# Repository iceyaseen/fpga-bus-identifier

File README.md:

# FPGA Communication Checker

A tool for figuring out how an unknown chip talks before you know anything about it. The usual situation: you have a small component with 3 or 4 pins, no datasheet, and no idea which protocol it speaks or what each pin does. Instead of guessing, you hook it up to this board and look at what actually happens on the lines.

## Status

The FPGA side is still in progress.

Working today:
- Edge capture on two probe channels, timestamped and streamed to a Python host over UART at 921600 baud.
- A framed, checksummed, self-resynchronising UART protocol between the FPGA and the host (start/stop/reset/status commands, edge records, ACK/ERROR replies).
- A from-scratch UART tx/rx pair, built and tested on the Tang Nano 9K.
- A 256-entry, block-RAM-backed capture FIFO, with high-water mark reported in the status reply.
- A PySide6 + pyqtgraph host GUI (dark instrument theme): live or offline (loaded from CSV) waveform view with pan/zoom/cursor/two draggable markers, a log-scale/zoomable pulse-width histogram, CSV export, and a "protocol hint" panel that reads the dominant pulse width and reports the closest matching clock/UART baud/1-Wire pulse - timing arithmetic only, not protocol decoding.
- An active I2C master: bidirectional open-drain probe drivers, software-switchable pull-ups, an electrical pre-scan (own pull-up / needs ours / held low / floating, per channel, before any bus traffic), and a 0x08-0x77 address sweep that reports every address that ACKs. Driven from the host's "Scan I2C" button; verified in simulation against a fake I2C slave (exactly one address found, START/STOP/ACK timing checked against spec) and confirmed on real hardware against an MLX90614 at 0x5A.

Not built yet:
- Reading actual data back from a found device (the I2C master currently only does the one-byte address-probe transaction a scan needs).
- Decoders for UART, 1-Wire, and PWM.
- Detection of analog (non-digital) devices - everything so far assumes the thing on the probes is digital.

## Host software

Requires Python 3 plus:
```
pip install PySide6 pyqtgraph pyserial
```
Then run:
```
python3 host/host.py [serial-port]
```
`host/protocol.py` holds the wire-format parser (framing, checksums, resync) and `host/hint.py` the protocol-hint arithmetic; both are plain Python with no GUI dependency, and each has a standalone test script (`host/test_frame_parser.py`, `host/test_hint.py`) that can be run without any hardware attached.

<p align="center">

<br>
<sup>Screenshot of a real capture, probed on P_A/P_B. Numbered callouts below.</sup>
</p>

1. **Sidebar** - connect, start/stop/reset capture, load/save CSV, show/hide the console.
2. **Waveform navigation** - zoom in/out, a window-width field with an adaptive ns/us/ms/s unit, step left/right, and Follow Latest (an oscilloscope-style roll-mode toggle, lit up green when on).
3. **Waveform view** - P_A/P_B drawn as square waves. Pan/zoom with the mouse, a crosshair cursor that follows it, and two draggable markers (dashed lines) with a live delta-t readout below the plot.
4. **Pulse-width histogram** - log-scale count axis, so a rare sharp spike (e.g. a 100 kHz clock) stays visible next to a much taller structureless smear instead of being flattened to nothing; the time axis is independently zoomable to reveal fine structure.
5. **Statistics + Protocol Hint** - live edge/pulse/gap stats, plus a hint that reads the histogram's dominant pulse width and checks it against known clocks, standard UART bauds, and 1-Wire timing. Pure arithmetic, never a claim to have identified a protocol - see the disclaimer printed under it.
6. **Console** (hidden by default) - the scrolling log, a raw-byte diagnostic mode, pause (freezes the view without losing anything), and clear.
7. **Status strip** - a link-alive dot that blinks while connected, live records/sec, FIFO high-water mark, a sticky overflow-since-reset dot, and the frame resync count (flagged only if resyncs happen well after connecting, not for the one-time settle that's normal when the FPGA is already transmitting at connect time).

## The PCB

A shield that sits on top of the Tang Nano 9K. Built and working, not just designed - the photos below are the real board. It has two probe channels and a 4-pin socket for the device under test.
<p align="center">

<br>
Each part on the probe lines is there for a specific reason:
</p>

- **220 ohm series resistor** on each probe line. The tool is meant to connect to devices whose voltage and drive strength are unknown, so the series resistor limits current if something unexpected is being driven.
- **Schottky clamp diodes (1N5819)** to 3.3V and GND on each probe line, so an over-voltage device can't reach the FPGA pin directly. Schottky specifically, not an ordinary diode: an ordinary diode clamps around 4.0V, which is already too high for this FPGA's inputs.
- **4.7k pull-ups switched by P-channel MOSFETs.** This is the part that needs explaining: to find out whether an unknown device already has its own pull-up, you need to disconnect ours first and see what the line does on its own. A fixed pull-up would make that measurement impossible, so it's switchable instead.
- **10k gate-to-source resistors** on those MOSFETs, so they stay off during the few milliseconds after power-up while the FPGA is still loading its bitstream and its pins are floating.

## Pin assignments

| Tang Nano 9K pin | Signal    | Notes |
|---|---|---|
| 54 | `ctrl_b`   | Active low. Pulling low turns on channel B's pull-up MOSFET. |
| 55 | `ctrl_a`   | Active low. Pulling low turns on channel A's pull-up MOSFET. |
| 56 | `probe_a`  | Probe channel A. |
| 57 | `probe_b`  | Probe channel B. |

Active low because these drive P-channel MOSFETs, which turn on when their gate is pulled low.

## Using it

Plug the unknown device into the 4-pin socket. A 4-pin device fills all four positions. A 3-pin device leaves `probe_a` empty.

## I2C scanning

Click **Scan I2C** in the host app. It runs two steps automatically:

1. **Electrical pre-scan** - before any bus traffic, each channel is classified purely by watching pull-up behaviour: *has its own pull-up* (reads high with ours off), *needs ours* (low/floating with ours off, clean high once ours switches on), *held low* (still low even with our pull-up on - a device driving it, or a short), or *floating* (unstable with no pull-up at all - nothing connected). This tells you whether the device is even I2C-shaped before wasting time on an address sweep.
2. **Address sweep** - START, address + write bit, check for ACK, STOP, for every address 0x08-0x77 (the valid 7-bit range). Every address that ACKs gets reported; an empty result is reported as "No devices found", not left ambiguous.

**Which probe is SDA and which is SCL is not auto-detected** - it's a host-side toggle ("SDA/SCL mapping: Normal (A=SDA, B=SCL) / Swapped (A=SCL, B=SDA)"), simpler and more transparent than guessing. If a scan against a known-good device finds nothing, flip the mapping and scan again. Verified against a real MLX90614 infrared thermometer (address 0x5A) on real hardware.

The scan's own generated I2C traffic is visible in the waveform view too (make sure capture is running - the "Scan I2C" button starts it automatically) - a good way to confirm the master is generating correct signals, not just trusting the reported result.

New host commands, single bytes like the existing ones (no framing needed on that side):

| Command | Effect |
|---|---|
| `A` / `a` | channel A pull-up on / off |
| `B` / `b` | channel B pull-up on / off |
| `N` / `W` | normal / swapped SDA-SCL pin mapping |
| `E` | run the electrical pre-scan |
| `I` | run the address sweep |

`E` and `I` are long-running, so unlike every other command their ACK is deferred until the operation actually finishes, not when the byte arrives - that's what lets the host safely chain pre-scan -> sweep off the pre-scan's own ACK. Two new frame types carry the results: `0xA9 PRESCAN_RESULT` (channel, category) and `0xAA ADDR_HIT` (one address that ACKed) - see `host/protocol.py` for the exact wire format, which follows the same `[MARKER][PAYLOAD][CHECKSUM]` scheme as everything else.

## Screenshots

<p align="center">

<br>
<sup>A real scan: the pre-scan found a pull-up already present on both channels, and the address sweep found one device, at 0x5A - a real MLX90614 infrared thermometer.</sup>
</p>

<p align="center">

<br>
<sup>The Tang Nano 9K wired up on a breadboard while testing against a real MLX90614.</sup>
</p>

General decoupling notes for this kind of breadboard setup: keep the 10uF bulk capacitor close to the 3.3V and GND rails it's decoupling, and keep the 100nF ceramic capacitor close to the sensor under test, not back at the FPGA end - it's there to filter noise right at the device, and a long lead defeats the point.

| Signal | Tang Nano 9K pin | Goes to |
|---|---|---|
| `probe_a` | 56 | Sensor SDA or SCL (depends on the SDA/SCL mapping setting) |
| `probe_b` | 57 | Sensor SCL or SDA (the other line) |
| `ctrl_a` | 55 | Channel A pull-up MOSFET gate |
| `ctrl_b` | 54 | Channel B pull-up MOSFET gate |
| 3.3V | - | Sensor VDD |
| GND | - | Sensor GND, common return |

Waveform and pulse-width-histogram screenshots of real captured I2C traffic, plus a contact-bounce histogram for comparison, are still to come - they need the hardware connected and, for the bounce case, a saved capture that doesn't exist yet.

## Known limitations

- Only single-ended protocols are in scope. CAN and RS-485 are differential and need a transceiver, so they're not supported.
- A completely unpowered unknown chip can't be identified from the outside. This tool only works on devices that respond when probed.
- There are two probe channels, so SPI (which needs more lines) isn't reachable yet.
- The protocol hint only measures timing. A 100 kHz clock could be I2C or SPI - the hint says "consistent with", it does not identify the protocol.

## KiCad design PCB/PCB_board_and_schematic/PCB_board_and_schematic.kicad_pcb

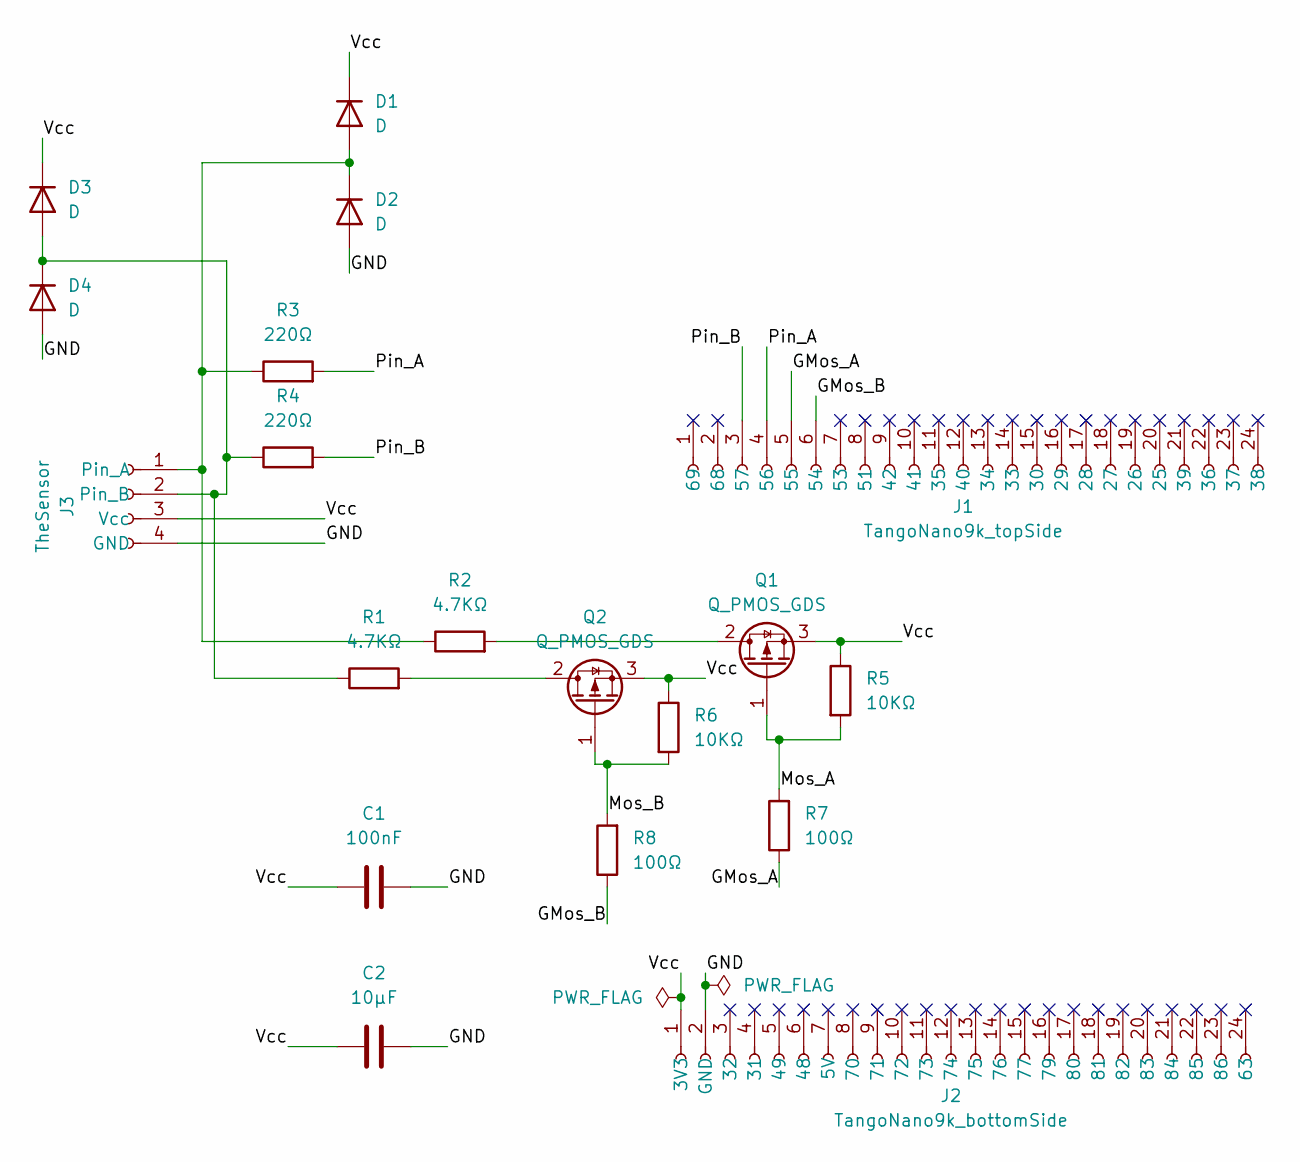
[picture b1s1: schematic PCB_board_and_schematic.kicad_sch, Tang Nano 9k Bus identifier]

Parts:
C1: 100nF; CP_Radial_D4.0mm_P1.50mm
C2: 10µF; CP_Radial_D5.0mm_P2.50mm
D1, D2, D3, D4: D; D_A-405_P7.62mm_Horizontal
J1: TangoNano9k_topSide; PinSocket_1x24_P2.54mm_Vertical
J2: TangoNano9k_bottomSide; PinSocket_1x24_P2.54mm_Vertical
J3: TheSensor; PinSocket_1x04_P2.54mm_Vertical
Q1, Q2: Q_PMOS_GDS; TO-220-3_Vertical
R1, R2: 4.7KΩ; R_Axial_DIN0204_L3.6mm_D1.6mm_P7.62mm_Horizontal
R3, R4: 220Ω; R_Axial_DIN0204_L3.6mm_D1.6mm_P7.62mm_Horizontal
R5, R6: 10KΩ; R_Axial_DIN0204_L3.6mm_D1.6mm_P7.62mm_Horizontal
R7, R8: 100Ω; R_Axial_DIN0204_L3.6mm_D1.6mm_P7.62mm_Horizontal

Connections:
/GMos_A: J1.5 (55), R7.1
/GMos_B: J1.6 (54), R8.1
/GND: C1.2, C2.2, D2.2 (A), D4.2 (A), J2.2 (GND), J3.4 (GND)
/Mos_A: Q1.1 (G), R5.2, R7.2
/Mos_B: Q2.1 (G), R6.2, R8.2
/Pin_A: J1.4 (56), R3.2
/Pin_B: J1.3 (57), R4.2
/Vcc: C1.1, C2.1, D1.1 (K), D3.1 (K), J2.1 (3V3), J3.3 (Vcc), Q1.3 (S), Q2.3 (S), R5.1, R6.1
unnamed: D1.2 (A), D2.1 (K), J3.1 (Pin_A), R2.1, R3.1
unnamed: D3.2 (A), D4.1 (K), J3.2 (Pin_B), R1.1, R4.1
unnamed: Q1.2 (D), R2.2
unnamed: Q2.2 (D), R1.2

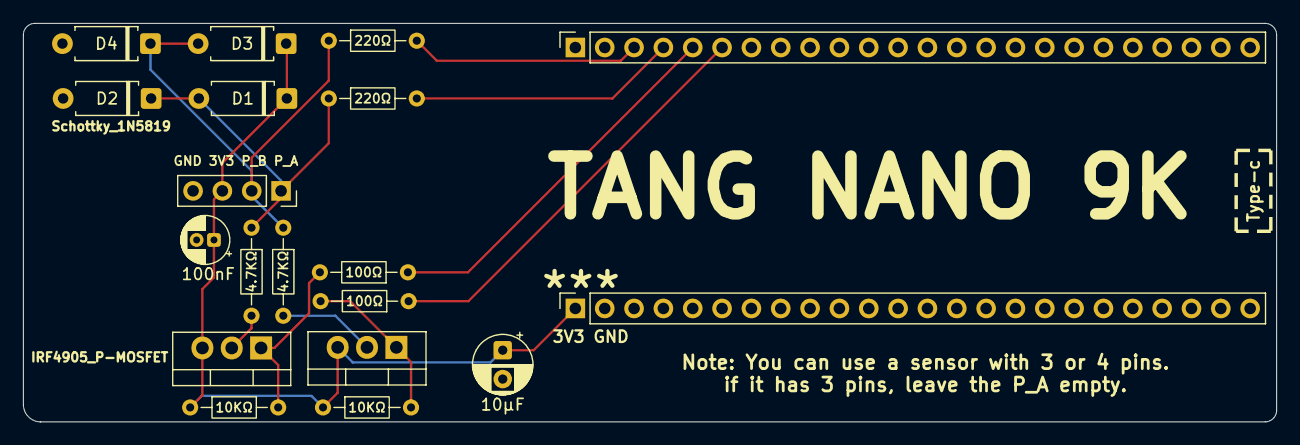
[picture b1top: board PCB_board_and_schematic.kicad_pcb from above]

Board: 2 copper layers, 108.5 x 34.5 mm, 19 parts (0 on the bottom side), 12 nets.
